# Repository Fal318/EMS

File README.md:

# RESS - Remote Emergency Stop Switch

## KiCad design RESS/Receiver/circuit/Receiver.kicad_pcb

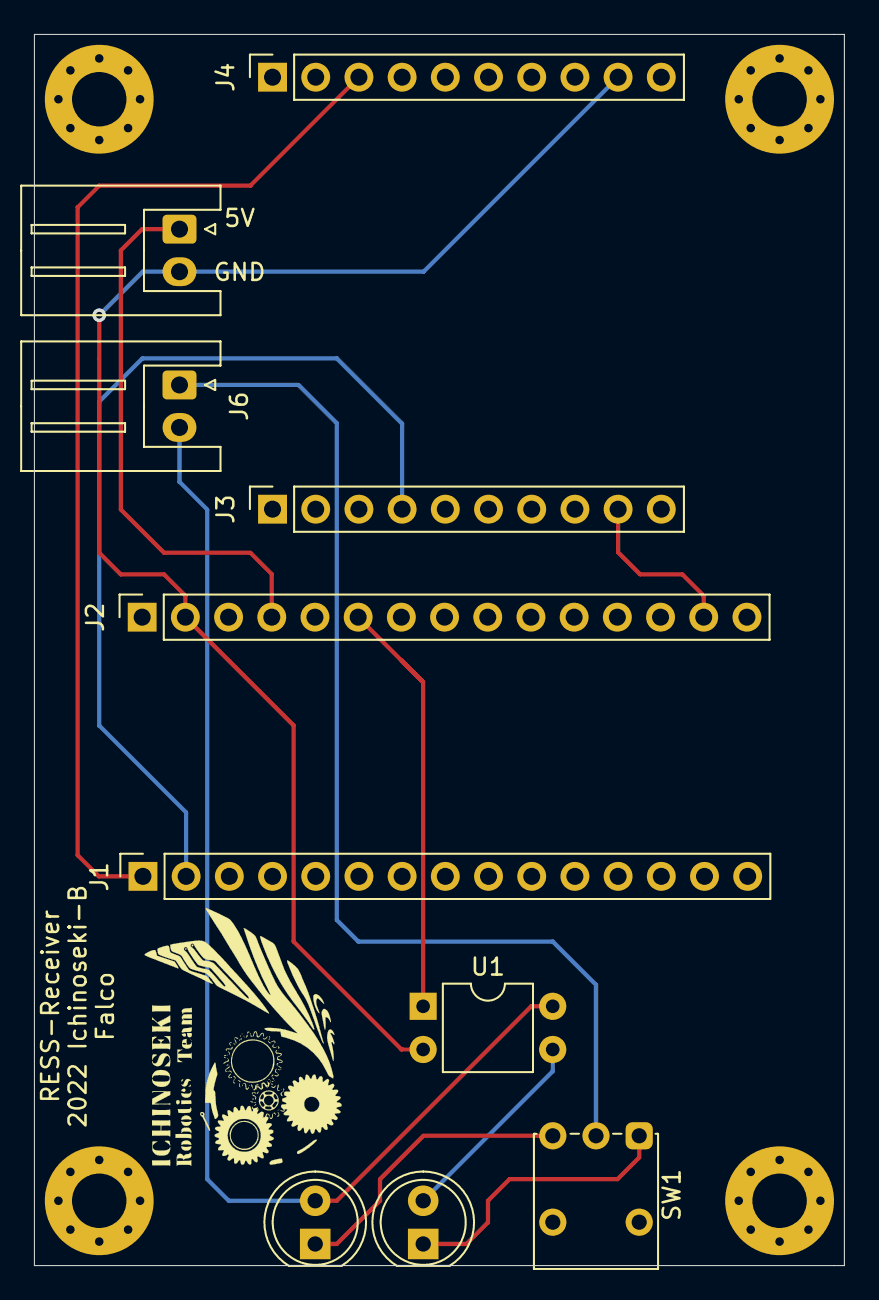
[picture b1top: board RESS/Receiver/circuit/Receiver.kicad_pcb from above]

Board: 2 copper layers, 47.6 x 72.4 mm, 15 parts (0 on the bottom side), 11 nets.

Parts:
D1, D2: LED; LED_D5.0mm
H1, H2, H3, H4: MountingHole; MountingHole_3.2mm_M3_Pad_Via
J1, J2: Conn_01x15_Female; PinSocket_1x15_P2.54mm_Vertical
J3: ADP_L; PinSocket_1x10_P2.54mm_Vertical
J4: ADP_R; PinSocket_1x10_P2.54mm_Vertical
J5: Power_IN; JST_XH_S2B-XH-A_1x02_P2.50mm_Horizontal
J6: RESS_OUT1; JST_XH_S2B-XH-A_1x02_P2.50mm_Horizontal
J8: Logo; INCT
SW1: SW_SPDT; SW_Push_1P2T_Vertical_E-Switch_800UDP8P1A1M6
U1: TLP785; DIP-4_W7.62mm

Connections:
+3V3: J2.14, J3.9
+5V: J2.4, J5.1
GND: J2.2, J4.9, J5.2, U1.2
unnamed: D1.1, SW1.1
unnamed: D1.2, U1.3
unnamed: D2.1, SW1.3
unnamed: D2.2, J6.2, U1.4
unnamed: J6.1, SW1.2
Out: J2.6, U1.1
RX: J1.2, J3.4
TX: J1.1, J4.3

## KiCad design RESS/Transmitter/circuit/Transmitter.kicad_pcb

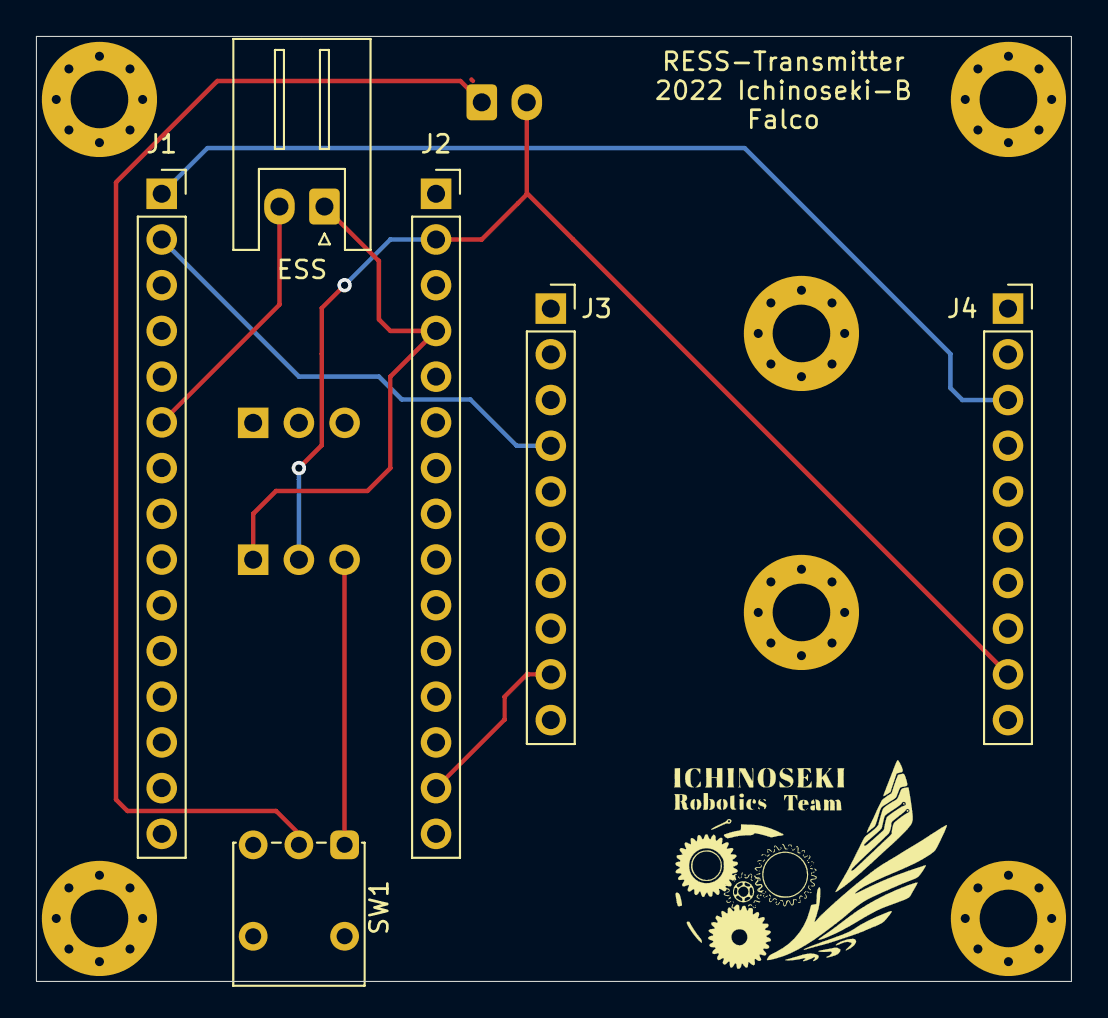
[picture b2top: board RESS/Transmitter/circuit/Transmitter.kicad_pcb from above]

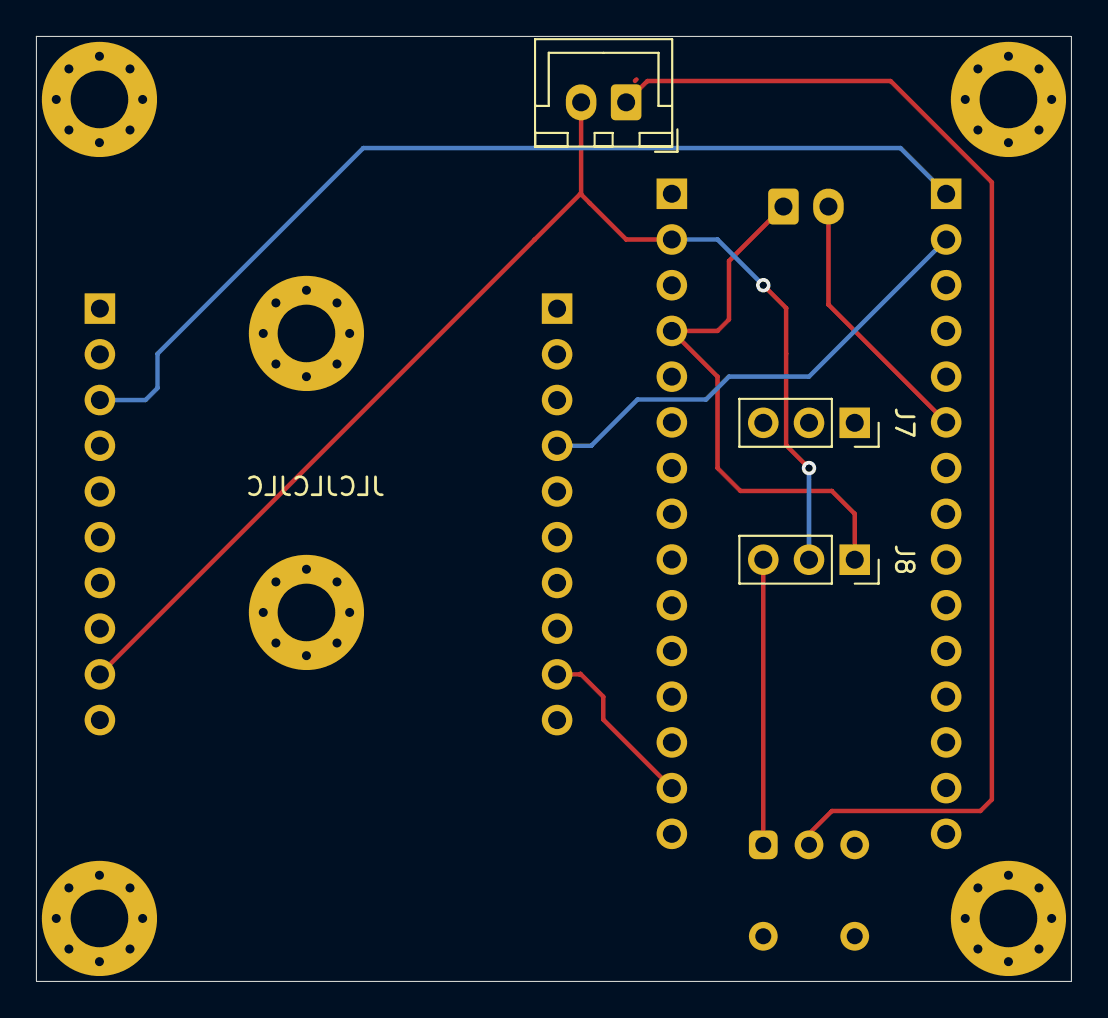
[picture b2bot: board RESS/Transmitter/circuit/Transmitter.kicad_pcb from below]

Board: 2 copper layers, 57.5 x 52.5 mm, 10 parts (3 on the bottom side), 8 nets.

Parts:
ESS: ESS_IN; JST_XH_S2B-XH-A_1x02_P2.50mm_Horizontal
J1, J2: Conn_01x15_Female; PinSocket_1x15_P2.54mm_Vertical
J3: ADP_L; PinSocket_1x10_P2.54mm_Vertical
J4: ADP_R; PinSocket_1x10_P2.54mm_Vertical
J5: POWER; JST_XH_B2B-XH-A_1x02_P2.50mm_Vertical
J7, J8#2: Conn_01x03_Female; PinSocket_1x03_P2.54mm_Vertical
J8: Logo; INCT
SW1: SW_SPDT; SW_Push_1P2T_Vertical_E-Switch_800UDP8P1A1M6

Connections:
+3V3: J2.14, J3.9
+5V: ESS.1, J2.4, J8#2.1
ESS_IN: ESS.2, J1.6
GND: J2.2, J4.9, J5.2, J8#2.2
PW_IN: J5.1, SW1.2
RX: J1.2, J3.4
TX: J1.1, J4.3
VCC: J8#2.3, SW1.1

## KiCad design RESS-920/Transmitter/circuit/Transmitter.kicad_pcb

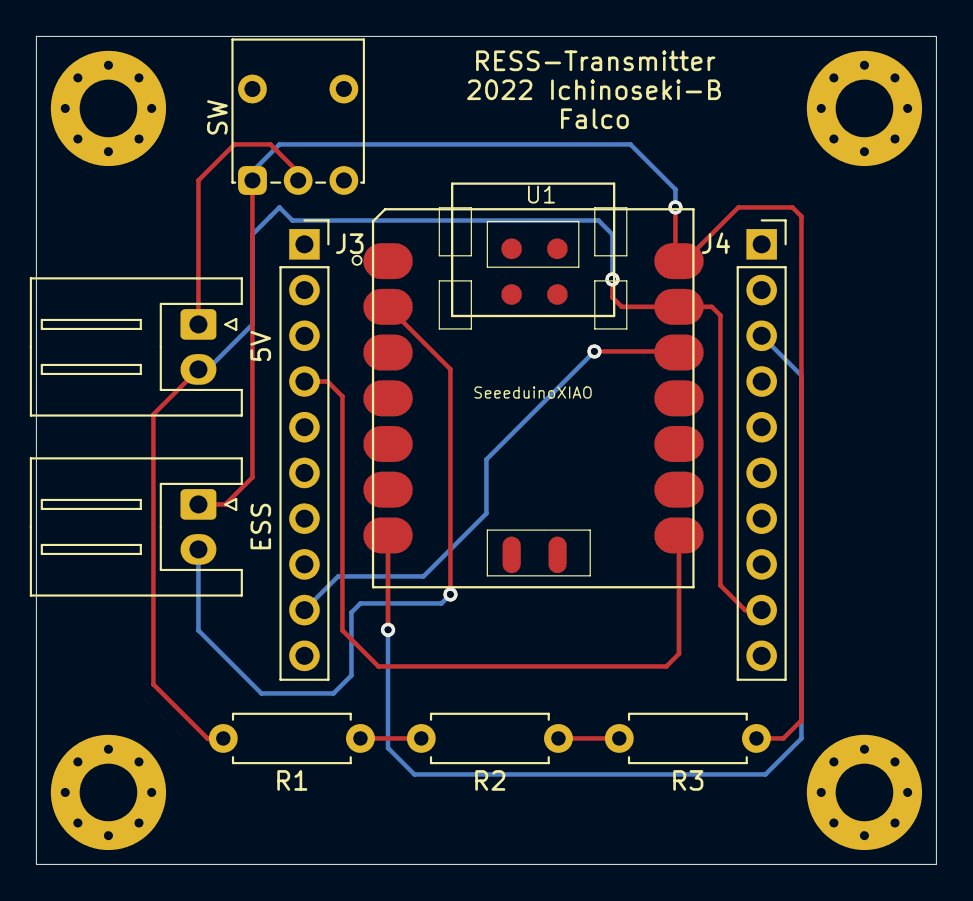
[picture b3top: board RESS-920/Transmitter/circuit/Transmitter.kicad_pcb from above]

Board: 2 copper layers, 50.0 x 46.0 mm, 9 parts (0 on the bottom side), 9 nets.

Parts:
5V: POWER; JST_XH_S2B-XH-A_1x02_P2.50mm_Horizontal
ESS: ESS_IN; JST_XH_S2B-XH-A_1x02_P2.50mm_Horizontal
J3: ADP_L; PinSocket_1x10_P2.54mm_Vertical
J4: ADP_R; PinSocket_1x10_P2.54mm_Vertical
R1, R2, R3: 18Ω; R_Axial_DIN0207_L6.3mm_D2.5mm_P7.62mm_Horizontal
SW: SW_SPDT; SW_Push_1P2T_Vertical_E-Switch_800UDP8P1A1M6
U1: SeeeduinoXIAO; Seeeduino XIAO-MOUDLE14P-2.54-21X17.8MM

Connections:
+3V3: J3.9, U1.12
+5V: ESS.1, R3.1, SW.1, U1.14
ESS_IN: ESS.2, U1.2
GND: 5V.2, J4.9, R1.2, U1.13
unnamed: R1.1, R2.2
unnamed: R2.1, R3.2
PW_IN: 5V.1, SW.2
RX: J3.4, U1.8
TX: J4.3, U1.7

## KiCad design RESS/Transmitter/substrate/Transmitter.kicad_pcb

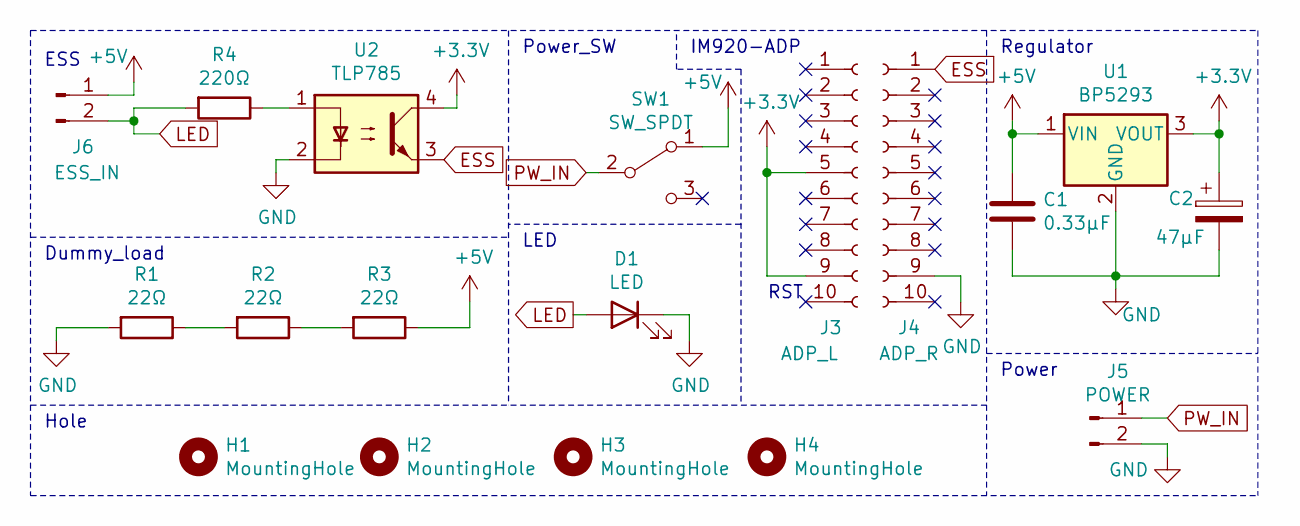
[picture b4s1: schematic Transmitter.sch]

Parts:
C1: 0.33μF; C_Rect_L4.0mm_W2.5mm_P2.50mm
C2: 47μF; CP_Radial_D5.0mm_P2.00mm
D1: LED; LED_D5.0mm
H1, H2, H3, H4: MountingHole; MountingHole_3.2mm_M3_Pad_Via
J3: ADP_L; PinSocket_1x10_P2.54mm_Vertical
J4: ADP_R; PinSocket_1x10_P2.54mm_Vertical
J5: POWER; JST_XH_S2B-XH-A_1x02_P2.50mm_Horizontal
J6: ESS_IN; JST_XH_S2B-XH-A_1x02_P2.50mm_Horizontal
R1, R2, R3: 22Ω; R_Axial_DIN0207_L6.3mm_D2.5mm_P7.62mm_Horizontal
R4: 220Ω; R_Axial_DIN0207_L6.3mm_D2.5mm_P7.62mm_Horizontal
SW1: SW_SPDT; SW_Push_1P2T_Vertical_E-Switch_800UDP8P1A1M6
U1: BP5293; TO-220-3_Horizontal_TabDown
U2: TLP785; DIP-4_W7.62mm

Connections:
+3V3: C2.1, J3.5, J3.9, U1.3 (VOUT), U2.4
+5V: C1.1, J6.1, R3.1, SW1.1 (A), U1.1 (VIN)
ESS: J4.1, U2.3
GND: C1.2, C2.2, D1.1 (K), J4.9, J5.2, R1.2, U1.2 (GND), U2.2
LED: D1.2 (A), J6.2, R4.2
unnamed: R1.1, R2.2
unnamed: R2.1, R3.2
unnamed: R4.1, U2.1
PW_IN: J5.1, SW1.2 (B)

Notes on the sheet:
RST
IM920-ADP
ESS
Power
Power_SW
Dummy_load
LED
Hole
Regulator

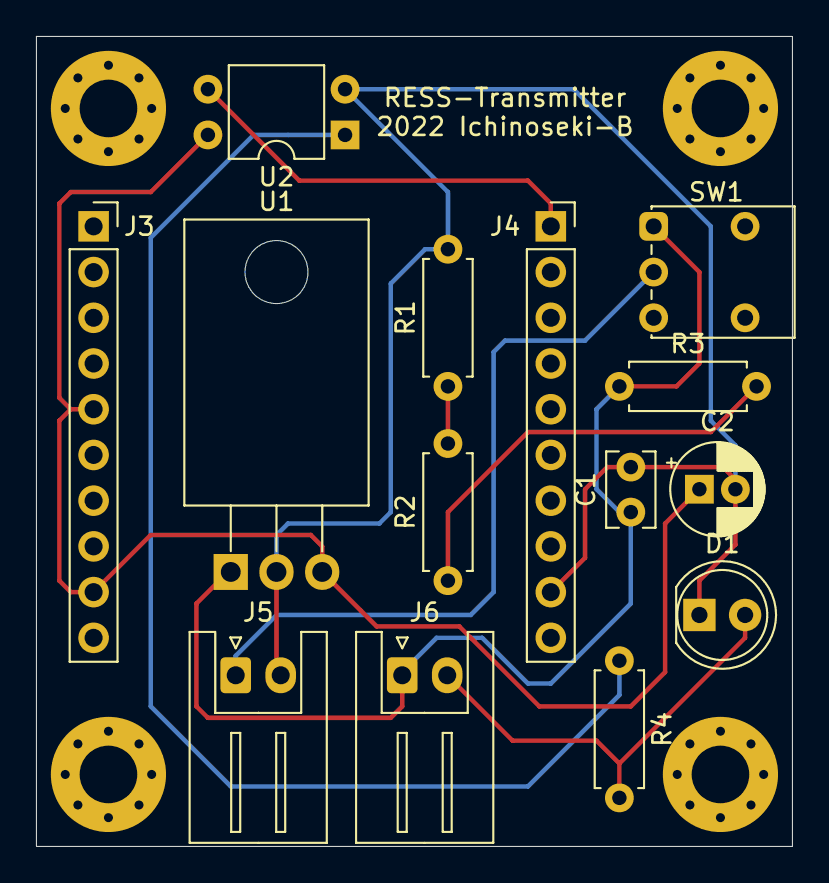
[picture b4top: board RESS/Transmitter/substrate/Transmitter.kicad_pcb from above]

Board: 2 copper layers, 42.0 x 45.0 mm, 18 parts (0 on the bottom side), 9 nets.

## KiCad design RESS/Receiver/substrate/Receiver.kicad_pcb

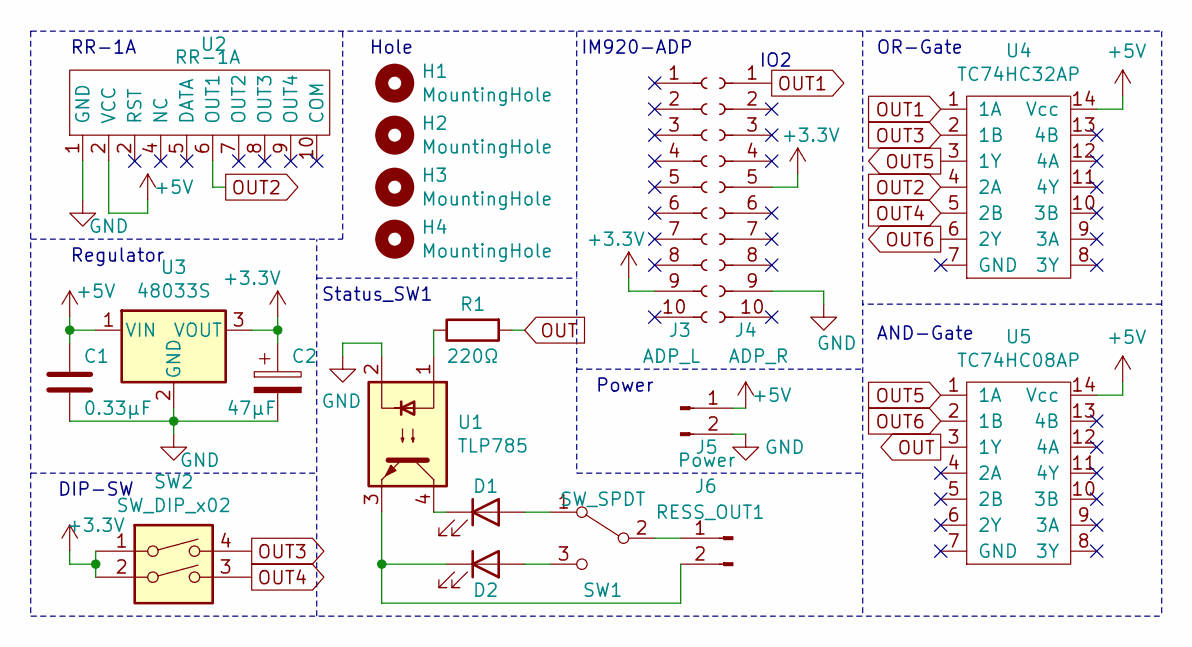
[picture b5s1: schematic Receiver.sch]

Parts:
C1: 0.33μF; C_Rect_L4.0mm_W2.5mm_P2.50mm
C2: 47μF; CP_Radial_D5.0mm_P2.00mm
D1, D2: LED; LED_D5.0mm
H1, H2, H3, H4: MountingHole; MountingHole_3.2mm_M3_Pad_Via
J3: ADP_L; PinSocket_1x10_P2.54mm_Vertical
J4: ADP_R; PinSocket_1x10_P2.54mm_Vertical
J5: Power; JST_XH_S2B-XH-A_1x02_P2.50mm_Horizontal
J6: RESS_OUT1; JST_XH_S2B-XH-A_1x02_P2.50mm_Horizontal
R1: 220Ω; R_Axial_DIN0207_L6.3mm_D2.5mm_P7.62mm_Horizontal
SW1: SW_SPDT; SW_Push_1P2T_Vertical_E-Switch_800UDP8P1A1M6
SW2: SW_DIP_x02; DIP-4_W7.62mm
U1: TLP785; DIP-4_W7.62mm
U2: RR-1A
U3: 48033S; TO-220-3_Horizontal_TabDown
U4: TC74HC32AP; DIP-14_W7.62mm
U5: TC74HC08AP; DIP-14_W7.62mm

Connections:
+3V3: C2.1, J3.9, J4.5, SW2.1, SW2.2, U3.3 (VOUT)
+5V: C1.1, J5.1, U2.2 (RST), U3.1 (VIN), U4.14 (Vcc), U5.14 (Vcc)
GND: C1.2, C2.2, J4.9, J5.2, U1.2, U2.1 (GND), U3.2 (GND)
unnamed: D1.1 (K), U1.4
unnamed: D1.2 (A), SW1.1 (A)
unnamed: D2.1 (K), J6.2, U1.3
unnamed: D2.2 (A), SW1.3 (C)
unnamed: J6.1, SW1.2 (B)
unnamed: R1.1, U1.1
OUT: R1.2, U5.3 (1Y)
OUT1: J4.1, U4.1 (1A)
OUT2: U2.6 (OUT1), U4.4 (2A)
OUT3: SW2.4, U4.2 (1B)
OUT4: SW2.3, U4.5 (2B)
OUT5: U4.3 (1Y), U5.1 (1A)
OUT6: U4.6 (2Y), U5.2 (1B)

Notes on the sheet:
Status_SW1
Power
IM920-ADP
Regulator
RR-1A
IO2
AND-Gate
OR-Gate
DIP-SW
Hole

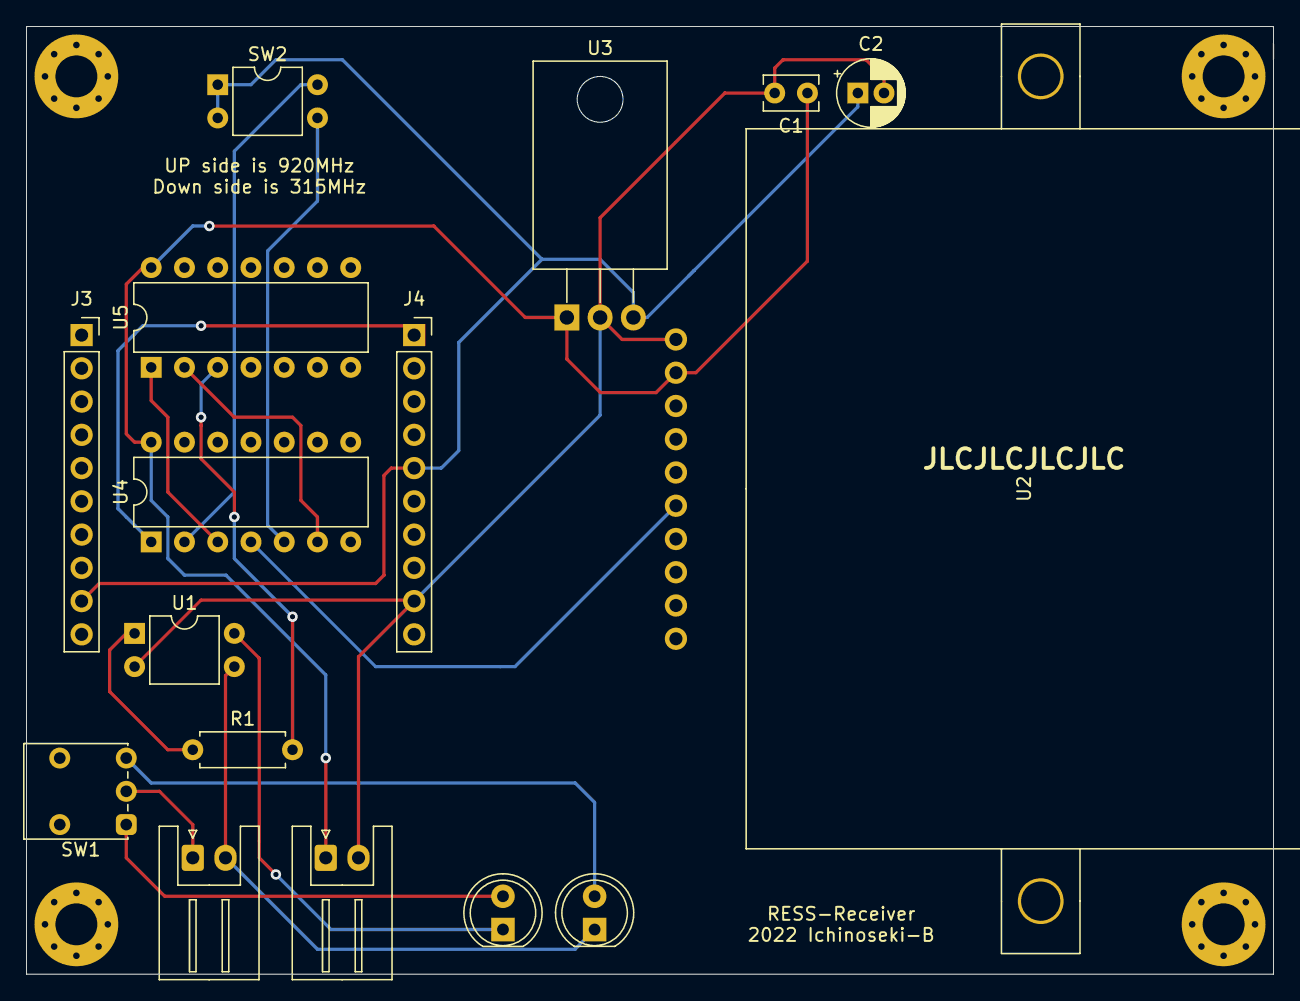
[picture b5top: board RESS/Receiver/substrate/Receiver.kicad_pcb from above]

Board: 2 copper layers, 95.3 x 72.4 mm, 20 parts (0 on the bottom side), 16 nets.

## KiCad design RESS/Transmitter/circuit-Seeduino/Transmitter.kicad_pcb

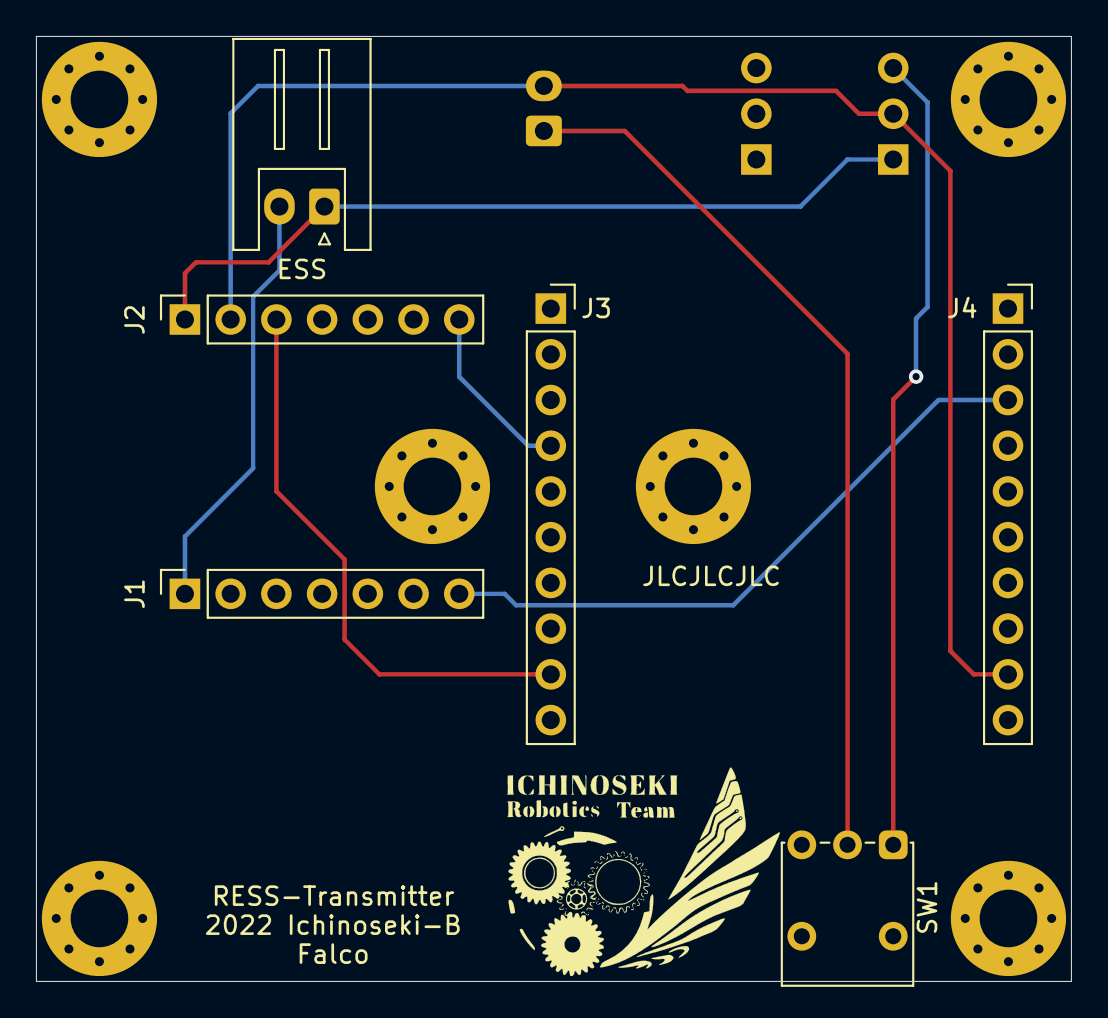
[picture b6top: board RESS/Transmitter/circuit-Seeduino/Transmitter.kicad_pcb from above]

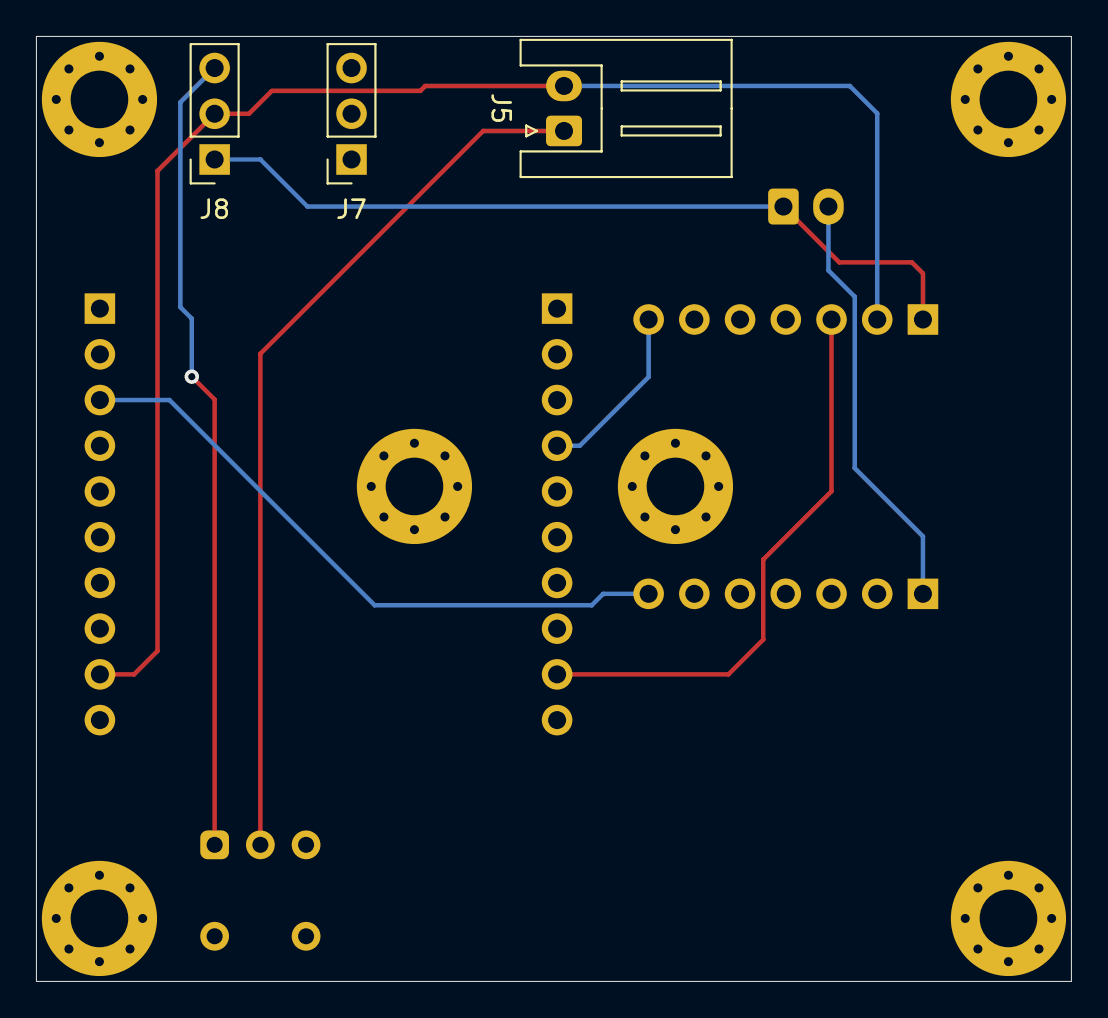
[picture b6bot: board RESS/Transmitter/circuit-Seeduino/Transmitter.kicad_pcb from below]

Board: 2 copper layers, 57.5 x 52.5 mm, 10 parts (3 on the bottom side), 8 nets.

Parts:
ESS: ESS_IN; JST_XH_S2B-XH-A_1x02_P2.50mm_Horizontal
J1, J2: Conn_01x07_Female; PinSocket_1x07_P2.54mm_Vertical
J3: ADP_L; PinSocket_1x10_P2.54mm_Vertical
J4: ADP_R; PinSocket_1x10_P2.54mm_Vertical
J5: POWER; JST_XH_S2B-XH-A_1x02_P2.50mm_Horizontal
J7, J8#2: Conn_01x03_Female; PinSocket_1x03_P2.54mm_Vertical
J8: Logo; INCT
SW1: SW_SPDT; SW_Push_1P2T_Vertical_E-Switch_800UDP8P1A1M6

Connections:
+3V3: J2.3, J3.9
+5V: ESS.1, J2.1, J8#2.1
ESS_IN: ESS.2, J1.1
GND: J2.2, J4.9, J5.2, J8#2.2
PW_IN: J5.1, SW1.2 (B)
RX: J2.7, J3.4
TX: J1.7, J4.3
VCC: J8#2.3, SW1.1 (A)

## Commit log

2021-07-12 ディレクトリの配置
2021-07-12 :construction: WIP
2021-07-15 3Dデータの追加
2021-08-27 基板の更新
2021-08-27 3Dデータの更新
2021-08-28 送信側のコードの更新
2021-08-30 設計の変更
2021-09-30 :construction:src
2021-09-30 :bug: Fix bug.
2021-10-21 :sparkles:Mbed OS6への移行
2022-06-15 Update transmitter.
2022-06-15 Update Receiver.
2022-06-16 Modify the PCB and add the Gerber files.
2022-06-16 Fix of interference part.
2022-06-30 ガーバーデータのzip化
2022-06-30 ディレクトリの変更
2022-07-08 マイコンを使用しない受信基板の追加
2022-07-08 P10を3.3Vと接続するのを忘れていたので修正
2022-07-08 送信基板の追加とファイルの整理
2022-07-09 回路の細かな修正
2022-07-09 RESS-920用コードの復元と余分なgitkeepの削除
2022-07-22 基板が燃えるほどのミスを修正
2022-08-14 ディレクトリの再配置
2022-08-14 ガーバーデータの追加
2022-08-23 DocStringにGitHubのURLを追加
2022-12-23 不要なファイルの整理
2023-01-24 バグの修正
    コールバック内でprintfを使用するとクラッシュしたのでprintfを削除した
